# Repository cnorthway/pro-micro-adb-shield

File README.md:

# Pro Micro ADB "Shield"

A simple PCB designed to add an Apple Desktop Bus (ADB) port to an Arduino
Pro Micro board to create a USB-ADB converter with a few extra features.
Uses mostly through-hole components.

Software is based on TMK's existing USB-ADB converter, see the
[firmware repo][fwrepo] for more details.

## Features
- DIP switch for on-the-fly modification of keymaps
- LEDs for Caps and Num Lock status
- Uses through hole components for ease of assembly (+ aesthetics, really)
- Based on a Pro Micro to avoid reinventing the atmega32 wheel, and to give
  some modicum of insurance against chip shortage insanity

## BOM / Assembly

Parts List:

| Ref.   | Description / Value                                                           |
| ------ | ----------------------------------------------------------------------------- |
| U1     | Arduino Pro Micro (5V)                                                        |
| J1     | 4 pin DIN socket, Kycon `KMDGX-4S-BS` or compatible                           |
| SW1    | Through-hole mini pushbutton, TE Connectivity `1825910-7` or compatible       |
| SW2    | 4 position surface mount DIP switch, CTS Electronics `214-LPST` or compatible |
| R1, R2 | 1/4 W through hole resistor, value dependent on LED                           |
| R3     | 1/4 W through hole resistor, 470 ohm (pullup for ADB, see [here][tmkwiki])    |
| D1, D2 | 3mm through-hole LEDs                                                         |

[tmkwiki]: https://github.com/tmk/tmk_keyboard/wiki/Apple-Desktop-Bus#pull-up-resistor

Steps:

1. Solder SMD DIP switch to shield
2. Solder all through hole parts to shield, trim legs
3. Short jumper on Pro Micro to set 5V logic levels
4. Solder headers to Pro Micro
5. Test LEDs, etc -- you won't be able to remove them later!
6. Stack boards together and solder headers to shield
7. Trim excess header length from shield side
8. Flash Pro Micro with [firmware][fwrepo]; optionally customize keymaps

[fwrepo]: https://github.com/cnorthway/tmk_keyboard/tree/cnorthway/adapter

## Note About 3D Models

I am not redistributing the third party 3D models, so if you want the full 3D
rendered experience: find them yourself, place them in a folder and add that
folder to Kicad with `Preferences->Configure Paths...` as `CUSTOM3D`.

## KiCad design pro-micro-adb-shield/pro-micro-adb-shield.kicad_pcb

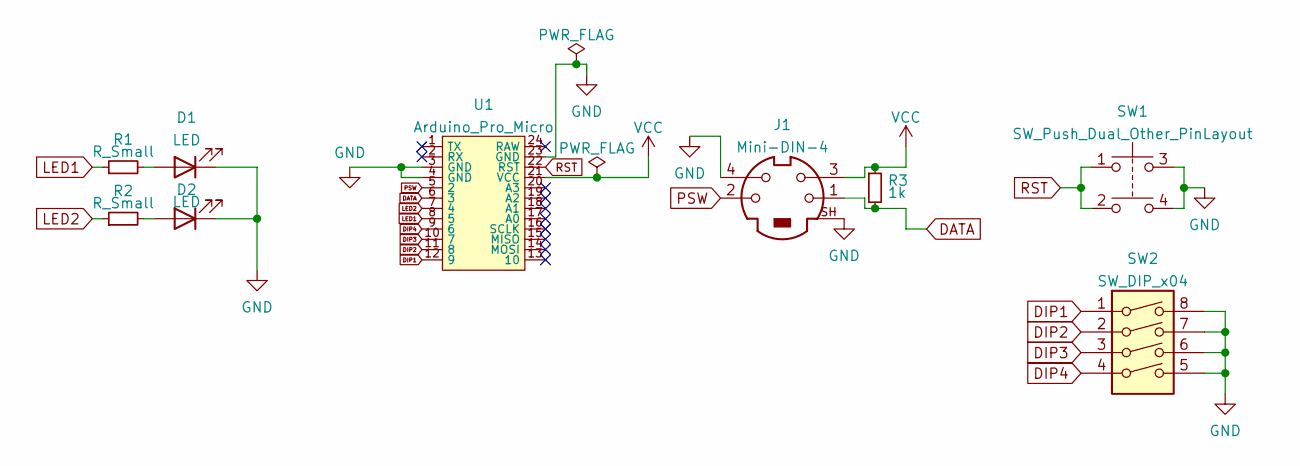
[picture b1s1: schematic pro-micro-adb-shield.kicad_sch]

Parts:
D1, D2: LED; LED_D3.0mm
J1: Mini-DIN-4; Mini-DIN-4_KMDGX-4S-BS
R1, R2: R_Small; R_Axial_DIN0207_L6.3mm_D2.5mm_P10.16mm_Horizontal
R3: 1k; R_Axial_DIN0207_L6.3mm_D2.5mm_P10.16mm_Horizontal
SW1: SW_Push_Dual_Other_PinLayout; SW_TH_Tactile_Omron_B3F-10xx
SW2: SW_DIP_x04; 218-4LPST
U1: Arduino_Pro_Micro

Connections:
DATA: J1.1, R3.2, U1.6 (3)
DIP1: SW2.1, U1.12 (9)
DIP2: SW2.2, U1.11 (8)
DIP3: SW2.3, U1.10 (7)
DIP4: SW2.4, U1.9 (6)
GND: D1.1 (K), D2.1 (K), J1.4, J1.SH, SW1.3, SW1.4, SW2.5, SW2.6, SW2.7, SW2.8, U1.3 (GND), U1.4 (GND), U1.23 (GND)
LED1: R1.1, U1.8 (5)
LED2: R2.1, U1.7 (4)
unnamed: D1.2 (A), R1.2
unnamed: D2.2 (A), R2.2
PSW: J1.2, U1.5 (2)
RST: SW1.1, SW1.2, U1.22 (RST)
VCC: J1.3, R3.1, U1.21 (VCC)

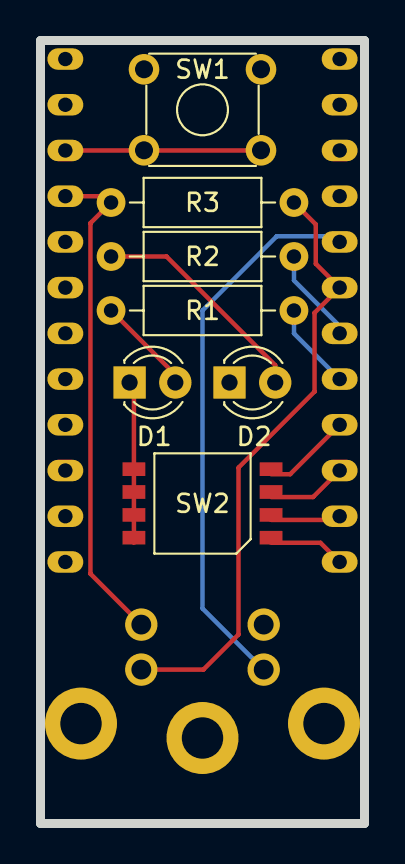
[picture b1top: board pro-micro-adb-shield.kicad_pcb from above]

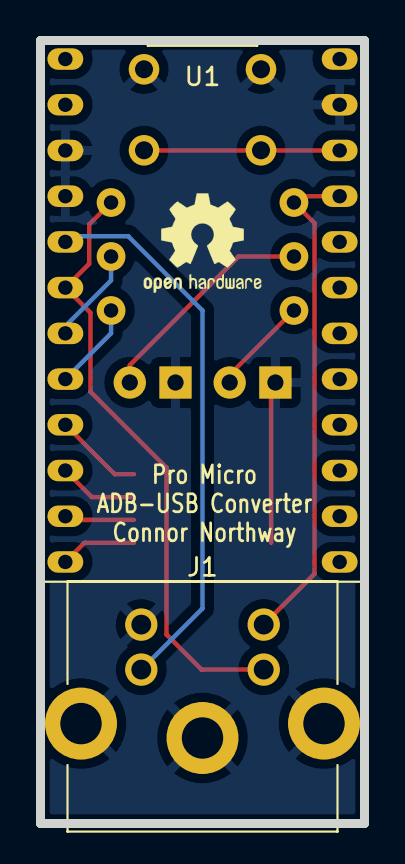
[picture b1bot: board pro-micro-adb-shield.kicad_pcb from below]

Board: 2 copper layers, 18.0 x 43.5 mm, 9 parts (2 on the bottom side), 13 nets.

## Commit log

2021-07-28 Create adapter PCB
2021-07-28 Add 3D model for switch, setup OSHPark constraints
2021-07-28 Modify edge cut, add silkscreen
2022-11-07 Fix shorted RST/GND through button
    why does this sort of thing always show up the day after you
    send the gerbers in to be manufactured >:(
2022-11-07 Use env var for 3d models, flip net names for DIP
2022-11-07 ignore backup directory
2022-11-07 Use built-in switch 3D model, make LED 3D flush
2022-11-07 Add README
    includes assembly instructions and parts list
2022-11-10 Add image to README
2022-11-10 Add note about 3D models
2022-11-10 DRC check
    remove one sneaky stub trace
    refill zones
    ignore screaming about silkscreen
2022-11-10 Add license
2022-11-10 Change pullup value in README
    just tried daisy chaining two devices for the first time using 4.7k,
    didn't work. swapped for 470 ohm, works great in all configurations
    probably more leeway, but 470 ohm seems to be reliable so i'll
    recommend that.
